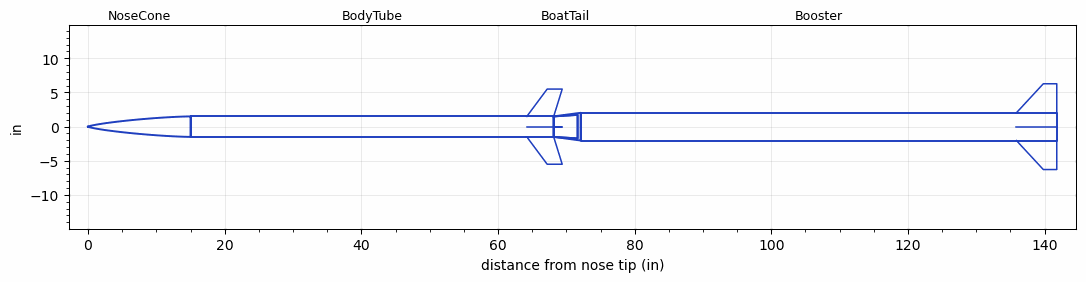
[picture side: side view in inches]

<RASAeroDocument>
 <FileVersion>2</FileVersion>
 <RocketDesign>
  <NoseCone>
   <Length>15</Length>
   <Diameter>3</Diameter>
   <Shape>Von Karman Ogive</Shape>
   <Location>0</Location>
  </NoseCone>
  <BodyTube>
   <Length>53.15</Length>
   <Diameter>3</Diameter>
   <Location>15</Location>
   <BoattailLength>3.5</BoattailLength>
   <BoattailRearDiameter>3.45</BoattailRearDiameter>
   <Fin>
    <Count>4</Count>
    <Chord>3.93</Chord>
    <Span>4</Span>
    <SweepDistance>2.975</SweepDistance>
    <TipChord>2.2</TipChord>
    <Thickness>0.118</Thickness>
    <Location>3.93</Location>
    <AirfoilSection>Hexagonal</AirfoilSection>
    <FX1>0.75</FX1>
    <FX3>0.75</FX3>
   </Fin>
  </BodyTube>
  <BoatTail>
   <Length>3.5</Length>
   <Diameter>3</Diameter>
   <RearDiameter>3.45</RearDiameter>
   <Location>68.15</Location>
  </BoatTail>
  <Booster>
   <Length>69.685</Length>
   <Diameter>4.055</Diameter>
   <InsideDiameter>3</InsideDiameter>
   <Location>68.15</Location>
   <ShoulderLength>3.937</ShoulderLength>
   <Fin>
    <Count>4</Count>
    <Chord>5.906</Chord>
    <Span>4.25</Span>
    <SweepDistance>3.94</SweepDistance>
    <TipChord>1.969</TipChord>
    <Thickness>0.118</Thickness>
    <Location>5.906</Location>
    <AirfoilSection>Hexagonal</AirfoilSection>
    <FX1>0.75</FX1>
    <FX3>0.75</FX3>
   </Fin>
  </Booster>
  <Surface>Smooth Paint</Surface>
  <ModifiedBarrowman>False</ModifiedBarrowman>
  <Turbulence>True</Turbulence>
  <UseBooster1>False</UseBooster1>
  <UseBooster2>False</UseBooster2>
 </RocketDesign>
 <LaunchSite>
  <Altitude>0</Altitude>
  <Pressure>0</Pressure>
  <RodAngle>0</RodAngle>
  <RodLength>16</RodLength>
  <Temperature>74</Temperature>
  <WindSpeed>0</WindSpeed>
 </LaunchSite>
 <Recovery>
  <Altitude1>1000</Altitude1>
  <Altitude2>1000</Altitude2>
  <DeviceType1>None</DeviceType1>
  <DeviceType2>None</DeviceType2>
  <Event1>False</Event1>
  <Event2>False</Event2>
  <Size1>1</Size1>
  <Size2>1</Size2>
  <EventType1>None</EventType1>
  <EventType2>None</EventType2>
  <CD1>1.33</CD1>
  <CD2>1.33</CD2>
 </Recovery>
 <SimulationList>
  <Simulation>
   <SustainerEngine>M2045-BS  (CTI)</SustainerEngine>
   <SustainerLaunchWt>18.91</SustainerLaunchWt>
   <SustainerNozzleDiameter>1.23</SustainerNozzleDiameter>
   <SustainerCG>48.43</SustainerCG>
   <SustainerIgnitionDelay>15</SustainerIgnitionDelay>
   <Booster1Engine>O3400-IM-P  (CTI)</Booster1Engine>
   <Booster1LaunchWt>63.88</Booster1LaunchWt>
   <Booster1SeparationDelay>0</Booster1SeparationDelay>
   <Booster1IgnitionDelay>0</Booster1IgnitionDelay>
   <Booster1CG>94.49</Booster1CG>
   <Booster1NozzleDiameter>1.75</Booster1NozzleDiameter>
   <IncludeBooster1>True</IncludeBooster1>
   <Booster2Delay>0</Booster2Delay>
   <IncludeBooster2>False</IncludeBooster2>
   <TimetoApogee>118.8057</TimetoApogee>
   <MaxAltitude>186002.5</MaxAltitude>
   <MaxVelocity>4081.333</MaxVelocity>
  </Simulation>
  <Simulation>
   <SustainerEngine>M685W-PS  (AT)</SustainerEngine>
   <SustainerLaunchWt>21.05</SustainerLaunchWt>
   <SustainerNozzleDiameter>1.23</SustainerNozzleDiameter>
   <SustainerCG>50</SustainerCG>
   <SustainerIgnitionDelay>20</SustainerIgnitionDelay>
   <Booster1Engine>N4000  (AT)</Booster1Engine>
   <Booster1LaunchWt>65.34</Booster1LaunchWt>
   <Booster1SeparationDelay>0</Booster1SeparationDelay>
   <Booster1IgnitionDelay>0</Booster1IgnitionDelay>
   <Booster1CG>96.46</Booster1CG>
   <Booster1NozzleDiameter>1.75</Booster1NozzleDiameter>
   <IncludeBooster1>True</IncludeBooster1>
   <Booster2Delay>0</Booster2Delay>
   <IncludeBooster2>False</IncludeBooster2>
   <TimetoApogee>126.9877</TimetoApogee>
   <MaxAltitude>187443.1</MaxAltitude>
   <MaxVelocity>3282.683</MaxVelocity>
  </Simulation>
 </SimulationList>
</RASAeroDocument>
